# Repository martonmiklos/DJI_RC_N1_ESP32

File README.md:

## DJI RC-N1 ESP32

This is a replacement PCB to the DJI RC-N1 (RC231) which features an ESP32.

Support for BLE toys is planned like Shell BBurago RC cars, LEGO 42410, etc.

It is WIP!

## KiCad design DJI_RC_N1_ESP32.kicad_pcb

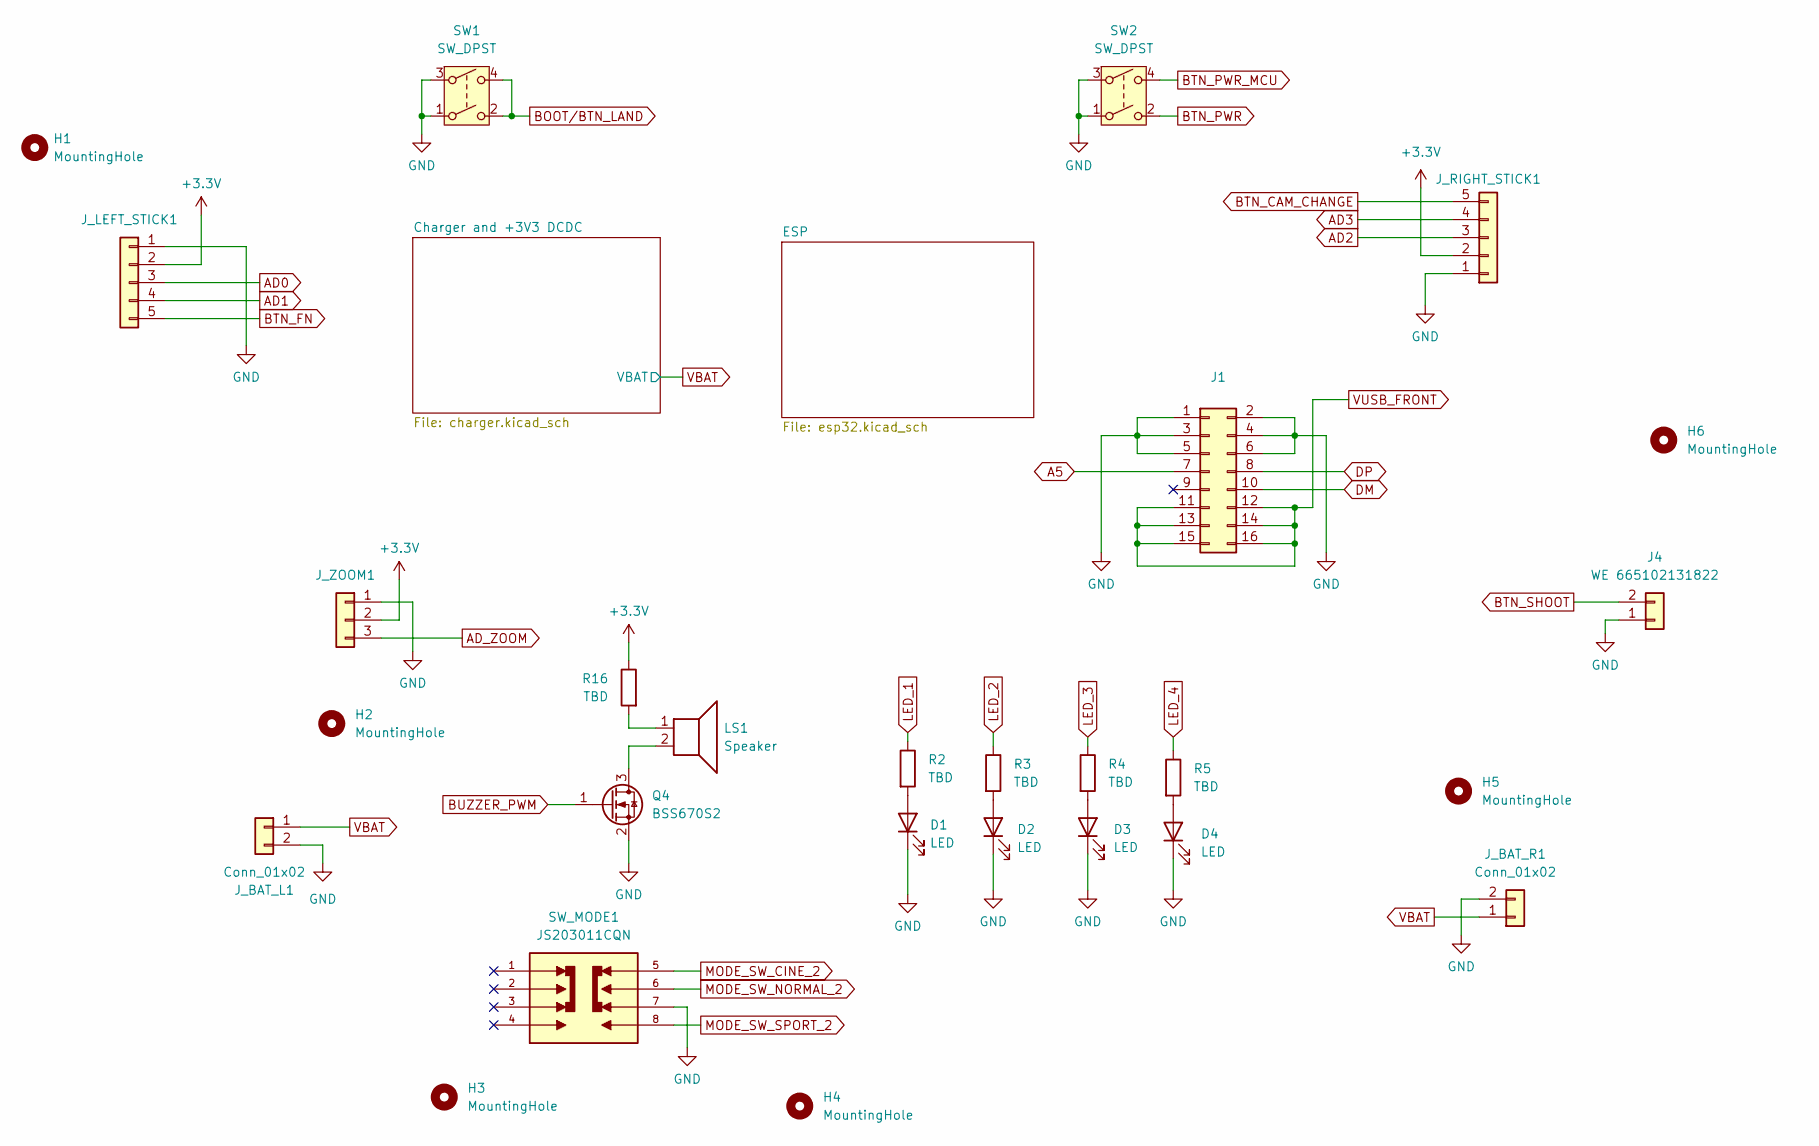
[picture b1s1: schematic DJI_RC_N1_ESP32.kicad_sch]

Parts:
D1, D2, D3, D4: LED; LED_0603_1608Metric
H1, H2, H3, H4, H5, H6: MountingHole; MountingHole_2mm
J1: Conn_02x08_Odd_Even
J4: WE 665102131822; J_Wurth_WR-WTB_665102131822
J_BAT_L1: Conn_01x02; CONN_S2B-ZR-SM4A-TFLFSN_JST
J_BAT_R1: Conn_01x02; CONN_S2B-ZR-SM4A-TFLFSN_JST
J_LEFT_STICK1: WE 665105131822; J_Wurth_WR-WTB_665105131822
J_RIGHT_STICK1: WE 665105131822; J_Wurth_WR-WTB_665105131822
J_ZOOM1: WE 665103131822; J_Wurth_WR-WTB_665103131822
LS1: Speaker; XDCR_CMT-9605-85T
Q4: BSS670S2; SOT-23
R2, R3, R4, R5, R16: TBD; R_0603_1608Metric
SW1, SW2: SW_DPST; SKRPABE010
SW_MODE1: JS203011CQN; SW_JS203011CQN; PARTREV VL

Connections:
+3.3V: J_LEFT_STICK1.2, J_RIGHT_STICK1.2, J_ZOOM1.2, R16.1; also elsewhere on the board
AD0: J_LEFT_STICK1.3; also elsewhere on the board
AD1: J_LEFT_STICK1.4; also elsewhere on the board
AD2: J_RIGHT_STICK1.3; also elsewhere on the board
AD3: J_RIGHT_STICK1.4; also elsewhere on the board
AD_ZOOM: J_ZOOM1.3; also elsewhere on the board
BOOT/BTN_LAND: SW1.2, SW1.4; also elsewhere on the board
BTN_CAM_CHANGE: J_RIGHT_STICK1.5; also elsewhere on the board
BTN_FN: J_LEFT_STICK1.5; also elsewhere on the board
BTN_PWR: SW2.2; also elsewhere on the board
BTN_PWR_MCU: SW2.4; also elsewhere on the board
BTN_SHOOT: J4.2; also elsewhere on the board
BUZZER_PWM: Q4.1 (G); also elsewhere on the board
GND: D1.1 (K), D2.1 (K), D3.1 (K), D4.1 (K), J1.1, J1.2, J1.3, J1.4, J1.5, J1.6, J4.1, J_BAT_L1.2, J_BAT_R1.2, J_LEFT_STICK1.1, J_RIGHT_STICK1.1, J_ZOOM1.1, Q4.2 (S), SW1.1, SW1.3, SW2.1, SW2.3, SW_MODE1.7; also elsewhere on the board
LED_1: R2.1; also elsewhere on the board
LED_2: R3.1; also elsewhere on the board
LED_3: R4.1; also elsewhere on the board
LED_4: R5.1; also elsewhere on the board
MODE_SW_CINE_2: SW_MODE1.5; also elsewhere on the board
MODE_SW_NORMAL_2: SW_MODE1.6; also elsewhere on the board
MODE_SW_SPORT_2: SW_MODE1.8; also elsewhere on the board
unnamed: D1.2 (A), R2.2
unnamed: D2.2 (A), R3.2
unnamed: D3.2 (A), R4.2
unnamed: D4.2 (A), R5.2
unnamed: J1.11, J1.12, J1.13, J1.14, J1.15, J1.16
unnamed: LS1.1, R16.2
unnamed: LS1.2, Q4.3 (D)
VBAT: J_BAT_L1.1, J_BAT_R1.1; also elsewhere on the board

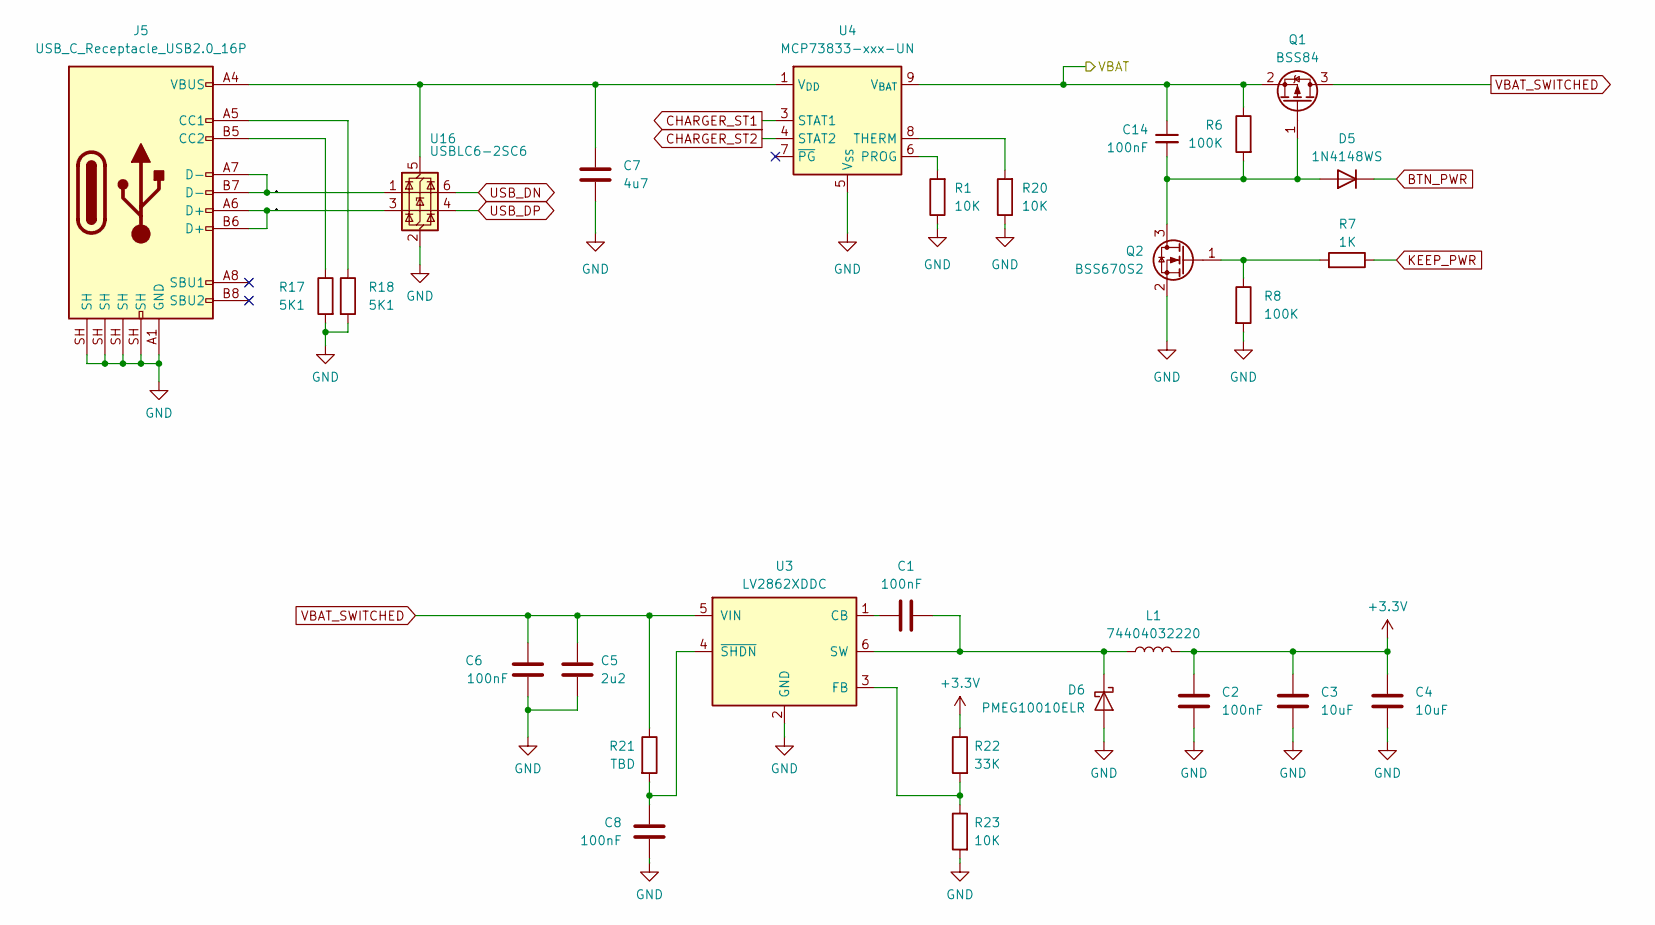
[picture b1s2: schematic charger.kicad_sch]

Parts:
C1, C2, C6, C8, C14: 100nF; C_0603_1608Metric
C3: 10uF; C_0603_1608Metric
C4: 10uF; C_0805_2012Metric
C5: 2u2; C_0805_2012Metric
C7: 4u7; C_0603_1608Metric
D5: 1N4148WS; D_SOD-323
D6: PMEG10010ELR; Nexperia_CFP3_SOD-123W
J5: USB_C_Receptacle_USB2.0_16P; USB_C_Receptacle_GCT_USB4085
L1: 74404032220; L_Wuerth_MAPI-3015
Q1: BSS84; SOT-23
Q2: BSS670S2; SOT-23
R1, R20, R23: 10K; R_0603_1608Metric
R6, R8: 100K; R_0603_1608Metric
R7: 1K; R_0603_1608Metric
R17, R18: 5K1; R_0603_1608Metric
R21: TBD; R_0603_1608Metric
R22: 33K; R_0603_1608Metric
U3: LV2862XDDC; SOT-23-6
U4: MCP73833-xxx-UN; MSOP-10_3x3mm_P0.5mm
U16: USBLC6-2SC6; SOT-23-6

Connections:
+3.3V: C2.2, C3.2, C4.2, L1.2, R22.1; also elsewhere on the board
/Charger and +3V3 DCDC/USB_UNPROT_DN: J5.A7 (D-), J5.B7 (D-), U16.1 (I/O1)
/Charger and +3V3 DCDC/USB_UNPROT_DP: J5.A6 (D+), J5.B6 (D+), U16.3 (I/O2)
BTN_PWR: D5.1 (K); also elsewhere on the board
CHARGER_ST1: U4.3 (STAT1); also elsewhere on the board
CHARGER_ST2: U4.4 (STAT2); also elsewhere on the board
GND: C2.1, C3.1, C4.1, C5.1, C6.1, C7.2, C8.1, D6.2 (A), J5.A1 (GND), J5.A12 (GND), J5.B1 (GND), J5.B12 (GND), J5.SH, Q2.2 (S), R1.1, R8.2, R17.2, R18.2, R20.1, R23.2, U3.2 (GND), U4.5 (V_{SS}), U16.2 (GND); also elsewhere on the board
KEEP_PWR: R7.1; also elsewhere on the board
unnamed: C14.2, D5.2 (A), Q1.1 (G), Q2.3 (D), R6.2
unnamed: C1.2, D6.1 (K), L1.1, U3.6 (SW)
unnamed: J5.A5 (CC1), R18.1
unnamed: J5.B5 (CC2), R17.1
unnamed: Q2.1 (G), R7.2, R8.1
unnamed: C1.1, U3.1 (CB)
unnamed: R22.2, R23.1, U3.3 (FB)
unnamed: C8.2, R21.2, U3.4 (~SHDN)
unnamed: R1.2, U4.6 (PROG)
unnamed: R20.2, U4.8 (THERM)
unnamed: C7.1, J5.A4 (VBUS), J5.A9 (VBUS), J5.B4 (VBUS), J5.B9 (VBUS), U4.1 (V_{DD}), U4.2 (V_{DD}), U16.5 (VBUS)
USB_DN: U16.6 (I/O1); also elsewhere on the board
USB_DP: U16.4 (I/O2); also elsewhere on the board
VBAT: C14.1, Q1.2 (S), R6.1, U4.9 (V_{BAT}), U4.10 (V_{BAT}); also elsewhere on the board
VBAT_SWITCHED: C5.2, C6.2, Q1.3 (D), R21.1, U3.5 (VIN)

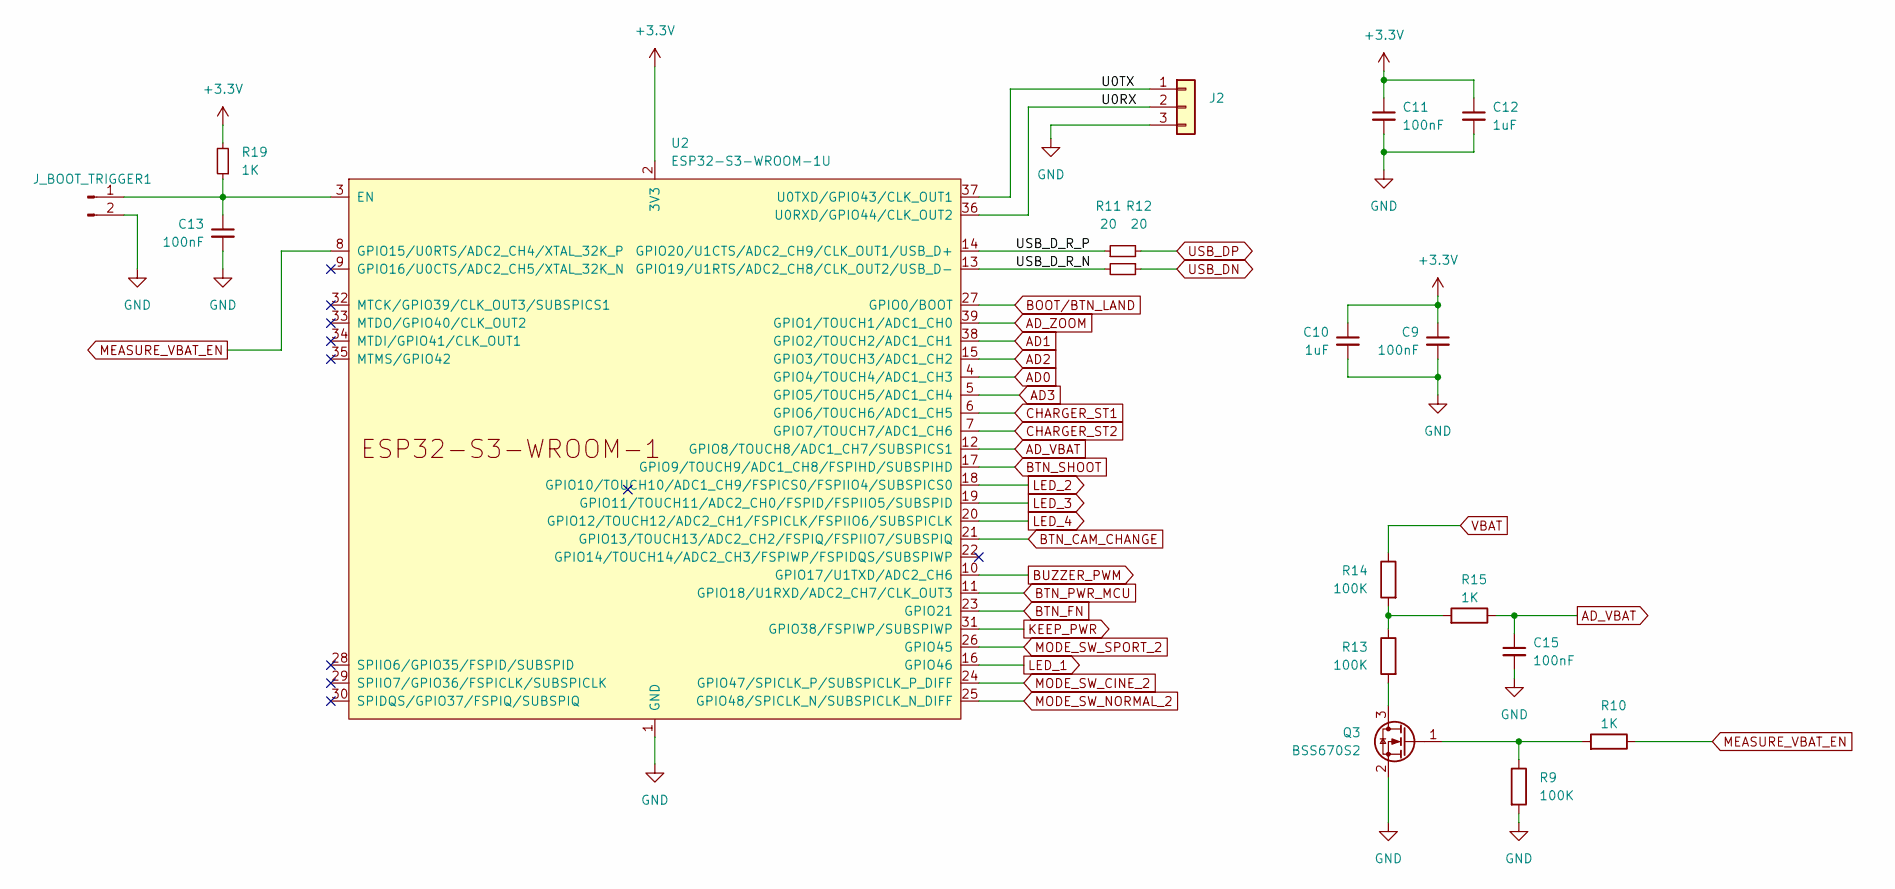
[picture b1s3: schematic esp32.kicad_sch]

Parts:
C9, C11, C13, C15: 100nF; C_0603_1608Metric
C10, C12: 1uF; C_0603_1608Metric
J2: Conn_01x03; PinHeader_1x03_P2.54mm_Vertical
J_BOOT_TRIGGER1: Conn_01x02_Pin; PinHeader_1x02_P2.00mm_Vertical
Q3: BSS670S2; SOT-23
R9, R13, R14: 100K; R_0603_1608Metric
R10, R15, R19: 1K; R_0603_1608Metric
R11, R12: 20; R_0603_1608Metric
U2: ESP32-S3-WROOM-1U

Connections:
+3.3V: C9.1, C10.1, C11.1, C12.1, R19.2, U2.2 (3V3); also elsewhere on the board
/ESP/U0RX: J2.2, U2.36 (U0RXD/GPIO44/CLK_OUT2)
/ESP/U0TX: J2.1, U2.37 (U0TXD/GPIO43/CLK_OUT1)
/ESP/USB_D_R_N: R12.2, U2.13 (GPIO19/U1RTS/ADC2_CH8/CLK_OUT2/USB_D-)
/ESP/USB_D_R_P: R11.1, U2.14 (GPIO20/U1CTS/ADC2_CH9/CLK_OUT1/USB_D+)
AD0: U2.4 (GPIO4/TOUCH4/ADC1_CH3); also elsewhere on the board
AD1: U2.38 (GPIO2/TOUCH2/ADC1_CH1); also elsewhere on the board
AD2: U2.15 (GPIO3/TOUCH3/ADC1_CH2); also elsewhere on the board
AD3: U2.5 (GPIO5/TOUCH5/ADC1_CH4); also elsewhere on the board
AD_VBAT: C15.1, R15.1, U2.12 (GPIO8/TOUCH8/ADC1_CH7/SUBSPICS1)
AD_ZOOM: U2.39 (GPIO1/TOUCH1/ADC1_CH0); also elsewhere on the board
BOOT/BTN_LAND: U2.27 (GPIO0/BOOT); also elsewhere on the board
BTN_CAM_CHANGE: U2.21 (GPIO13/TOUCH13/ADC2_CH2/FSPIQ/FSPIIO7/S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); also elsewhere on the board
BTN_FN: U2.23 (GPIO21); also elsewhere on the board
BTN_PWR_MCU: U2.11 (GPIO18/U1RXD/ADC2_CH7/CLK_OUT3); also elsewhere on the board
BTN_SHOOT: U2.17 (GPIO9/TOUCH9/ADC1_CH8/FSPIHD/SUBSPIHD); also elsewhere on the board
BUZZER_PWM: U2.10 (GPIO17/U1TXD/ADC2_CH6); also elsewhere on the board
CHARGER_ST1: U2.6 (GPIO6/TOUCH6/ADC1_CH5); also elsewhere on the board
CHARGER_ST2: U2.7 (GPIO7/TOUCH7/ADC1_CH6); also elsewhere on the board
GND: C9.2, C10.2, C11.2, C12.2, C13.2, C15.2, J2.3, J_BOOT_TRIGGER1.2, Q3.2 (S), R9.2, U2.1 (GND), U2.40 (GND), U2.41 (GND); also elsewhere on the board
KEEP_PWR: U2.31 (GPIO38/FSPIWP/SUBSPIWP); also elsewhere on the board
LED_1: U2.16 (GPIO46); also elsewhere on the board
LED_2: U2.18 (GPIO10/TOUCH10/ADC1_CH9/FSPICS0/FSPIIO4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); also elsewhere on the board
LED_3: U2.19 (GPIO11/TOUCH11/ADC2_CH0/FSPID/FSPIIO5/S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); also elsewhere on the board
LED_4: U2.20 (GPIO12/TOUCH12/ADC2_CH1/FSPICLK/FSPIIO6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); also elsewhere on the board
MEASURE_VBAT_EN: R10.1, U2.8 (GPIO15/U0RTS/ADC2_CH4/XTAL_32K_P)
MODE_SW_CINE_2: U2.24 (GPIO47/SPICLK_P/SUBSPICLK_P_DIFF); also elsewhere on the board
MODE_SW_NORMAL_2: U2.25 (GPIO48/SPICLK_N/SUBSPICLK_N_DIFF); also elsewhere on the board
MODE_SW_SPORT_2: U2.26 (GPIO45); also elsewhere on the board
unnamed: C13.1, J_BOOT_TRIGGER1.1, R19.1, U2.3 (EN)
unnamed: Q3.3 (D), R13.2
unnamed: Q3.1 (G), R9.1, R10.2
unnamed: R13.1, R14.2, R15.2
USB_DN: R12.1; also elsewhere on the board
USB_DP: R11.2; also elsewhere on the board
VBAT: R14.1; also elsewhere on the board

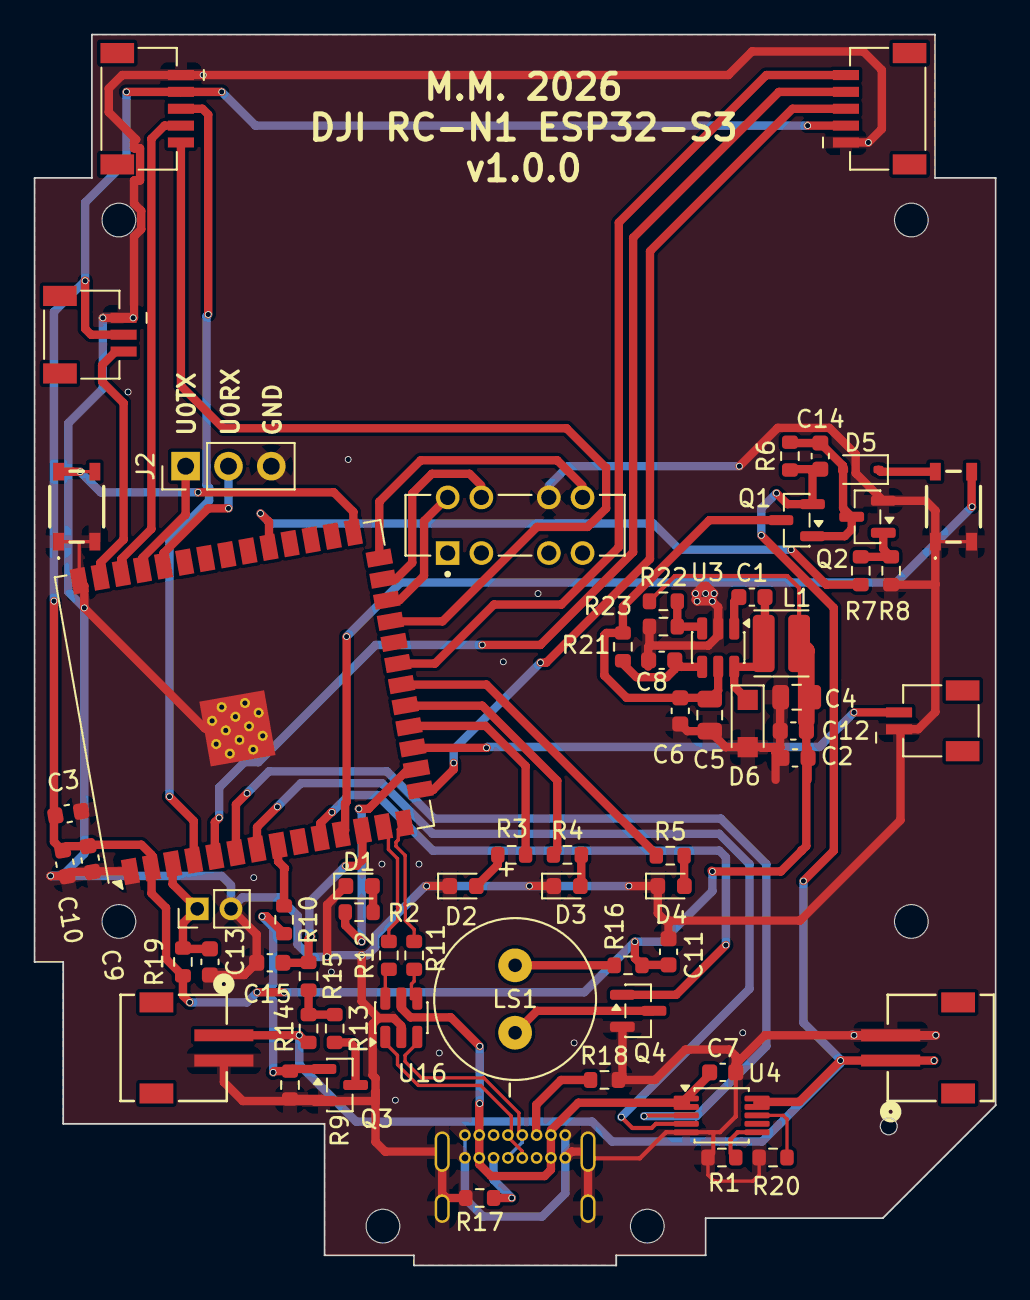
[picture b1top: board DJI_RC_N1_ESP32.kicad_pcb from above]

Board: 2 copper layers, 57.0 x 73.0 mm, 72 parts (1 on the bottom side), 57 nets.
